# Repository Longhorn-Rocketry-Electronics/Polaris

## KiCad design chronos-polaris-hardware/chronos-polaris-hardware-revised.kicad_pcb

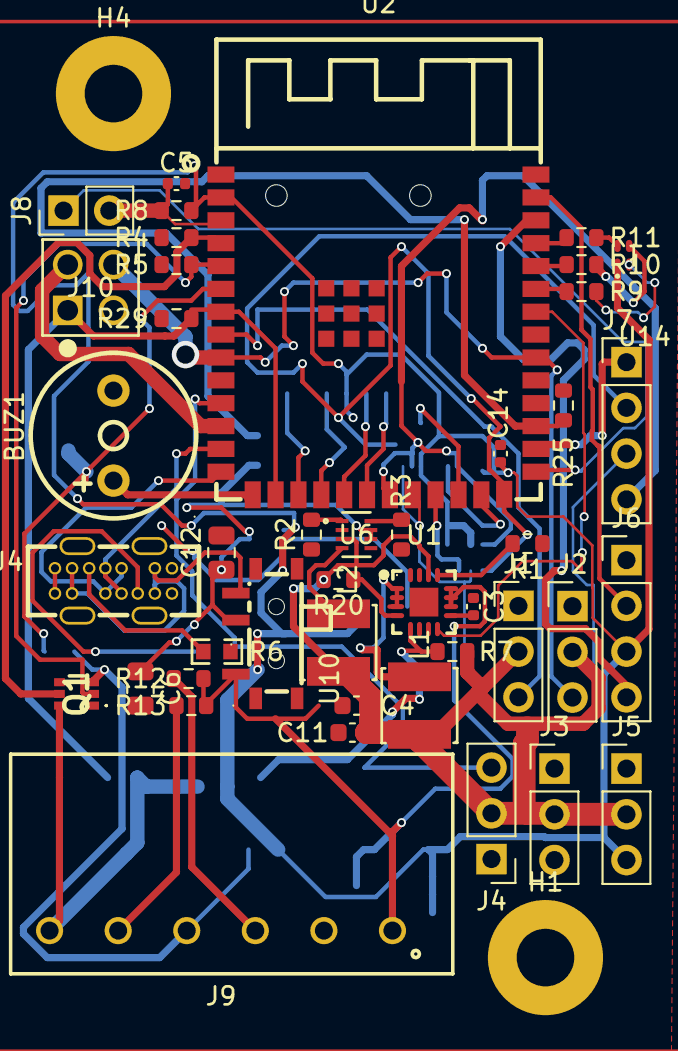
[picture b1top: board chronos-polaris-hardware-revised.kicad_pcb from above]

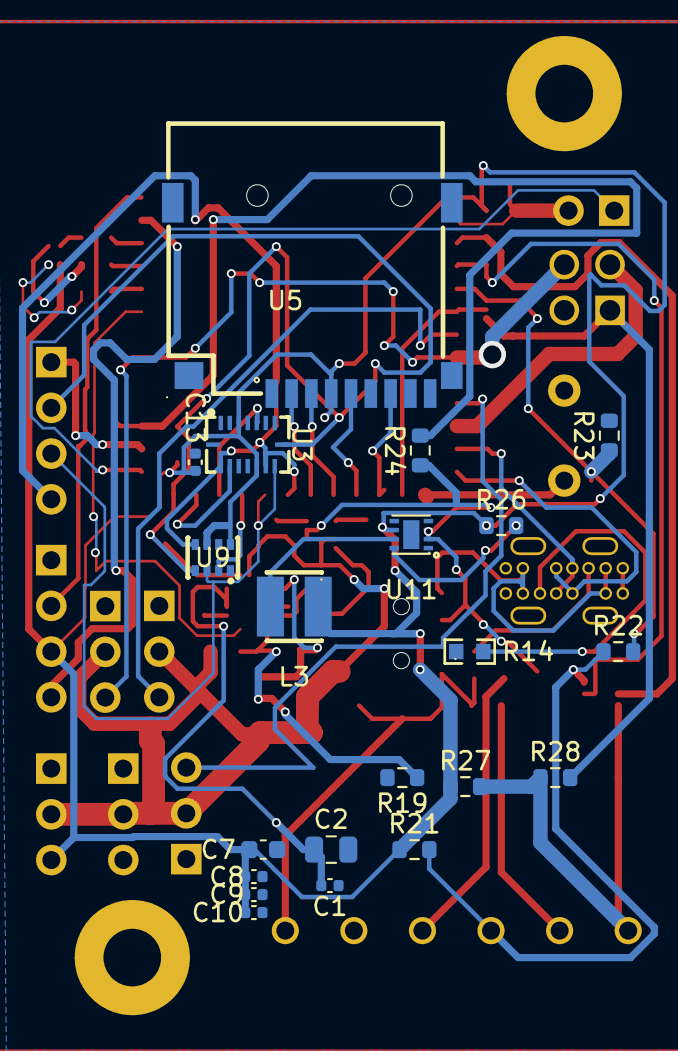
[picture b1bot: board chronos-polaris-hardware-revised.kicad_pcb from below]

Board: 2 copper layers, 66 parts (21 on the bottom side), 56 nets.

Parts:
BUZ1: HNB09A03; BUZ-TH_BD9.0-P5.00-D0.6-FD
C1, C5, C8, C9, C10, C13, C14: 100nF; C_0402_1005Metric
C2, C6: 10uF; C_0805_2012Metric
C3: 3.3nF; C_0402_1005Metric
C4, C7, C11: 22uF; C_0603_1608Metric
C12: 4.7uF; C_0805_2012Metric
H1, H4: MountingHole; MountingHole_3.2mm_M3_Pad
J1, J2, J3, J4, J5: Conn_01x03_Pin; PinHeader_1x03_P2.54mm_Vertical
J6, J7: Conn_01x04; PinHeader_1x04_P2.54mm_Vertical
J8: Conn_01x02; PinHeader_1x02_P2.54mm_Vertical
J9: 691417320006S
J10: TSW-102-07-G-D; TSW-102-07-G-D_SAI
L1, L2: 2.2uH; IND-SMD_L4.0-W4.0
L3: 2.2uH; IND-SMD_L3.0-W3.0
Q1: US6K4TR
R1, R4, R5, R8, R21, R23, R25, R27, R29: 10k; R_0603_1608Metric
R2: 240k; R_0603_1608Metric
R3: 27.4k; R_0603_1608Metric
R6, R14: 0603WAF5101T5E; R0603
R7: 160k; R_0603_1608Metric
R9, R10: 51; R_0603_1608Metric
R11: 100; R_0603_1608Metric
R12, R13: ?; R_0603_1608Metric
R19, R22, R24, R28: 30k; R_0603_1608Metric
R20, R26: 100k; R_0603_1608Metric
U1: TLV62130RGTR; QFN-16_L3.0-W3.0-P0.50-TL-EP
U2: ESP32; WIRELM-SMD_ESP32-S3-WROOM-1
U3: BMI088; LGA-16_L4.5-W3.0-P0.50-BL
U4: TYPE-C_14PLC-H10_0; USB-C-TH_SHOUHAN_TYPE-C-14PLC-H10.0
U5: TF_PUSH; TF-SMD_TF-PUSH
U6: TPS629206DRLR; SOT5X3-8_DRL_TEX
U9: BMP280; LGA-8_L2.5-W2.0-P0.65_AMP6127
U10: MSK12C02-HB; SW-TH_MSK12C02-HB-1
U11: TPS62172DSGR; WSON-8_L2.0-W2.0-P0.50-TL-EP
U14: FC-B1010RGBT-HG; LED-ARRAY-SMD_4P-L1.0-W1.0-TR-RD

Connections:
3.3V: C7.1, C8.1, C9.1, C10.1, C13.1, C14.1, J5.3, J6.3, L3.2, R8.2, R21.1, R26.1, R27.1, U2.2 (3V3), U3.3 (VDD), U3.11 (VDDIO), U5.4 (VDD), U9.6 (VDDIO), U9.8 (VDD), U11.6 (VOS), U14.1 (+)
5V: C4.1, C11.2, J1.2, J2.2, J3.2, J4.2, J5.2, L1.1, L2.1, R7.1, R20.2, U1.14 (VOS), U6.3 (VOS)
5V_5%BOOST: U1.8 (DEF), U2.34 (IO41)
/ACCEL CS: U2.25 (IO34), U3.14 (CSB1)
/BAT+: C1.2, C2.1, J9.1, R12.1, R13.1, U1.10 (AVIN), U1.11 (PVIN), U1.12 (PVIN), U10.1
/BMP CS: U2.23 (IO21), U9.2 (CSB)
/BUZ_CTRL: BUZ1.1 (+), U2.15 (IO3)
/DROGUE DETECT: J10.1, R28.2, R29.1, U2.7 (IO7), U2.16 (IO46)
/DROGUE V+: J9.5, R13.2
/GPIO0 (BOOTLOADER): J8.1, U2.27 (IO0)
/GYRO CS: U2.24 (IO33), U3.5 (CSB2)
/MAIN DETECT: R22.2, R23.1, U2.6 (IO6)
/MAIN V+: J9.3, R12.2
/MISO / SDO: J7.4, U2.21 (IO13), U3.10 (SDO2), U3.15 (SDO1), U9.5 (SDO)
/MOSI / SDI: J7.3, U2.22 (IO14), U3.9 (SDA/SDI), U9.3 (SDI)
/RESET: C5.1, J8.2, R8.1, U2.3 (EN)
/SPI CLK: J7.2, U2.26 (IO45), U3.8 (SCL/SCK), U9.4 (SCK)
/TypeC/IO19: U2.13 (IO19), U4.A6 (D+), U4.B6 (D+)
/TypeC/IO20: U2.14 (IO20), U4.A7 (D-), U4.B7 (D-)
/USB_5V: U4.A4 (VBUS), U4.A9 (VBUS), U4.B4 (VBUS), U4.B9 (VBUS), U10.3
/Voltage Divider/DROGUE_V+: J9.6, Q1.6 (TR1_D), R27.2, R28.1
/Voltage Divider/MAIN V+: J9.4, Q1.3 (TR2_D), R21.2, R22.1
GND: BUZ1.2 (-), C1.1, C2.2, C3.1, C4.2, C5.2, C6.2, C7.2, C8.2, C9.2, C10.2, C11.1, C12.2, C13.2, C14.2, J1.1, J2.1, J3.1, J3.3, J4.1, J5.1, J6.1, J9.2, J10.3, Q1.1 (TR1_S), Q1.4 (TR2_S), R1.1, R2.1, R3.2, R4.1, R5.1, R6.1, R14.1, R19.2, R23.2, R25.2, R29.2, U1.6 (AGND), U1.7 (FSW), U1.15 (PGND), U1.16 (PGND), U1.17 (EXP), U2.1 (GND), U2.10 (IO17), U2.31 (IO38), U2.40 (GND), U2.41 (GND), U3.2 (NC), U3.4 (GNDA), U3.6 (GNDIO), U3.7 (PS), U4.A1 (GND), U4.A12 (GND), U4.B1 (GND), U4.B12 (GND), U5.6 (VSS), U6.5 (GND), U9.1 (GND), U9.7 (GND), U11.1 (PGND), U11.4 (AGND), U11.5 (FB), U11.9 (EP)
unnamed: J1.3, U2.8 (IO15)
unnamed: J2.3, J10.4, U2.9 (IO16), U2.32 (IO39)
unnamed: J4.3, U2.11 (IO18)
unnamed: J6.2, U2.39 (IO1)
unnamed: J6.4, U2.38 (IO2)
unnamed: J7.1, U2.28 (IO35)
unnamed: L1.2, U1.1 (SW), U1.2 (SW), U1.3 (SW)
unnamed: Q1.2 (TR1_G), R5.2, U2.5 (IO5)
unnamed: Q1.5 (TR2_G), R4.2, U2.4 (IO4)
unnamed: R9.1, U14.4 (-)
unnamed: R10.1, U14.3 (-)
unnamed: R11.1, U14.2 (-)
unnamed: R1.2, U1.13 (EN)
unnamed: R7.2, R19.1, U1.5 (FB)
unnamed: R20.1, U1.4 (PG)
unnamed: C3.2, U1.9 (SS/TR)
unnamed: J10.2, U2.12 (IO8)
unnamed: U2.17 (IO9), U5.7 (DAT0)
unnamed: U2.18 (IO10), U5.5 (CLX)
unnamed: U2.19 (IO11), U5.3 (CMD)
unnamed: U2.20 (IO12), U5.2 (CD/DAT3)
unnamed: R9.2, U2.35 (IO42)
unnamed: R10.2, U2.36 (RXD0)
unnamed: R11.2, U2.37 (TXD0)
unnamed: R14.2, U4.A5 (CC1)
unnamed: R6.2, U4.B5 (CC2)
unnamed: R2.2, U6.1 (FB/VSET)
unnamed: R3.1, U6.8 (MODE/S-CONF)
unnamed: L2.2, U6.4 (SW)
unnamed: R26.2, U11.8 (PG)
unnamed: L3.1, U11.7 (SW)
VIN: C6.1, C12.1, R24.1, U6.6 (VIN), U6.7 (EN), U10.2, U11.2 (VIN), U11.3 (EN)
VIN_1/4: R24.2, R25.1, U2.29 (IO36)

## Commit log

2023-07-01 add symbols and footprints
2023-07-02 mainly finish schematic
2023-07-03 checkpoint, mcu needs to be replaced
2023-07-04 finish schematic for real, start pcb
2023-07-04 convert ematch detect to voltage divider
2023-07-06 finish PCB layout
2023-07-06 improve ground planes
2023-07-12 switch to compact 5v regulator
2023-07-12 fix V in switching with usb, remove diode
2023-07-12 polaris routing with fix V
2023-07-12 minor fixes
2023-07-12 silkscreen
2023-07-29 random qol updates?
2023-08-01 add some firmware
2023-08-01 all hardware working
2023-08-04 testing rocket hardware
2023-08-04 add working logging (all hw works)
2023-08-07 quaternion integration post processor
    added gyroToAngle.m and ROCKcopy version, both are the same
2023-08-17 significantly improved code
2023-09-25 fix massive logging bug
2023-10-15 fix altitudes not being relative to each other
2023-10-29 Initial commit to branch
2023-10-29 switch detect bufs to uint16_t
2023-11-14 switched altitude based deployment to use median altitude to avoids spikes
2023-11-16 fix compile issue
2024-03-02 Launch Day Firmware Version
2024-03-02 Actual Launch Day Firmware
2024-03-06 Add template servo code
2024-03-06 Ignore kicad zip backups
2024-08-27 Improve orientation tracking; add servo support, fake TVC
2024-10-20 update version
2024-10-27 test
2024-10-27 Cleaned up Pressure Sensor and StepDownConverter. - Rishik B.
2024-10-27 changed label names. - Rishik B.
2024-10-27 combined jazeb changes into mine. - Rishik B.
2024-10-27 Added Type C. Need to integrate Dual-PNP-Small-Signal-Transistor.kicad_sch
2024-10-27 asdf
2024-10-27 made satvik fixes
2024-11-03 clean up
2024-11-03 E-match lowside switch
2024-11-10 highside to lowside
2024-11-10 Fixed warnings and error messages. - Rishik B.
2024-11-10 fix transistor pinout wrong
2024-11-10 update part
2024-11-10 fixing pcb
2024-11-10 another footprint
2024-11-10 wwew
2024-11-10 end it all
2024-11-10 finnaly
2024-11-17 abcd
2024-11-17 pcb revert
    a
2024-11-17 pcb update again
2025-01-30 flight ready code
2025-02-14 Add files via upload
    added by Vraj
2025-02-14 Add files via upload
    both schematic and pct
2025-02-15 added footprint
    footprint added for rigel connector. now all we need is to draw traces, layout, then ready for submit to jlcpcb
2025-02-16 fix merge conflicts . - Rishik B.
2025-02-16 added the mount to board (no connecitons yet)
2025-02-17 MATLAB polaris alt and state analysis code, some polaris datasets
2025-02-17 added drone data
2025-02-17 PCB should be done with some minor design problems maybe - Rishik B
2025-02-17 updated border. - Rishik B.
2025-02-17 fixed the border. - Rishik B.
2025-02-23 Schematic Changes as per DR1 Suggestions
2025-02-28 Added Direct Datasheet Links
    (except for pressure sensor AMP2167, I couldn't find a pdf datasheet)
2025-02-28 fixes. - Rishik B.
2025-03-07 Quick fix
2025-04-04 UART code needs to be tested
